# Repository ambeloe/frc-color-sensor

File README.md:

# frc-color-sensor
a compatible replacement for the rev robotics v3 color sensor that also includes the ST VL53L1X distance sensor

should be fully compatible with the v3 sensor including using the same cable

# design is not tested or complete

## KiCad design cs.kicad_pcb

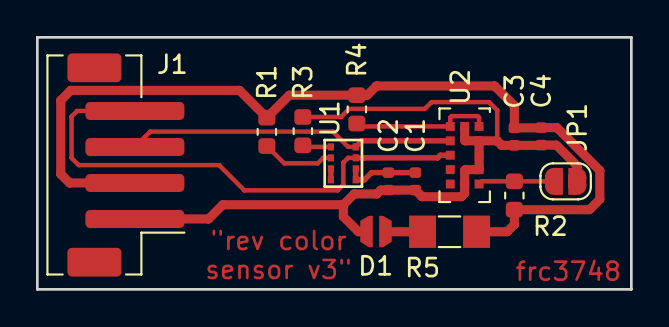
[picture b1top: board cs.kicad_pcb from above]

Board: 2 copper layers, 33.0 x 14.0 mm, 14 parts (0 on the bottom side), 10 nets.

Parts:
C1, C3: 10uF; C_0402_1005Metric
C2: 100nF; C_0402_1005Metric
C4: 100nf; C_0402_1005Metric
D1: mp1616
J1: JST_PH4x2mm; JST_PH_B4B-PH-SM4-TB_1x04-1MP_P2.00mm_Vertical
JP1: Jumper; SolderJumper-2_P1.3mm_Open_RoundedPad1.0x1.5mm
R1, R2: 4.7k; R_0603_1608Metric
R3, R4: 0R; R_0603_1608Metric
R5: 22R; R_MiniMELF_MMA-0204
U1: APDS-9151
U2: VL53L1CXV0FY_1; ST_VL53L1X

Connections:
+3V3: C1.2, C2.2, C3.1, C4.1, J1.2, R1.1, R2.1, R4.2, R5.1, U1.5, U1.6
GND: C1.1, C2.1, C3.2, C4.2, D1.1, J1.1, JP1.1, R3.1, U2.2, U2.3, U2.4, U2.6, U2.12
unnamed: D1.2, R5.2
unnamed: J1.3, U1.8, U2.10
unnamed: J1.4, U1.7, U2.9
unnamed: JP1.2, R2.2, U2.5
unnamed: R1.2, U1.2
unnamed: R3.2, U1.1
unnamed: R4.1, U2.1, U2.11
unnamed: U1.3, U1.4

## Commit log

2020-02-11 initial upload (untested)
2020-02-11 made readme
2020-02-17 added led and fixed the apds-9151 not having a connection to vcc
2020-02-17 github formatting is hard
